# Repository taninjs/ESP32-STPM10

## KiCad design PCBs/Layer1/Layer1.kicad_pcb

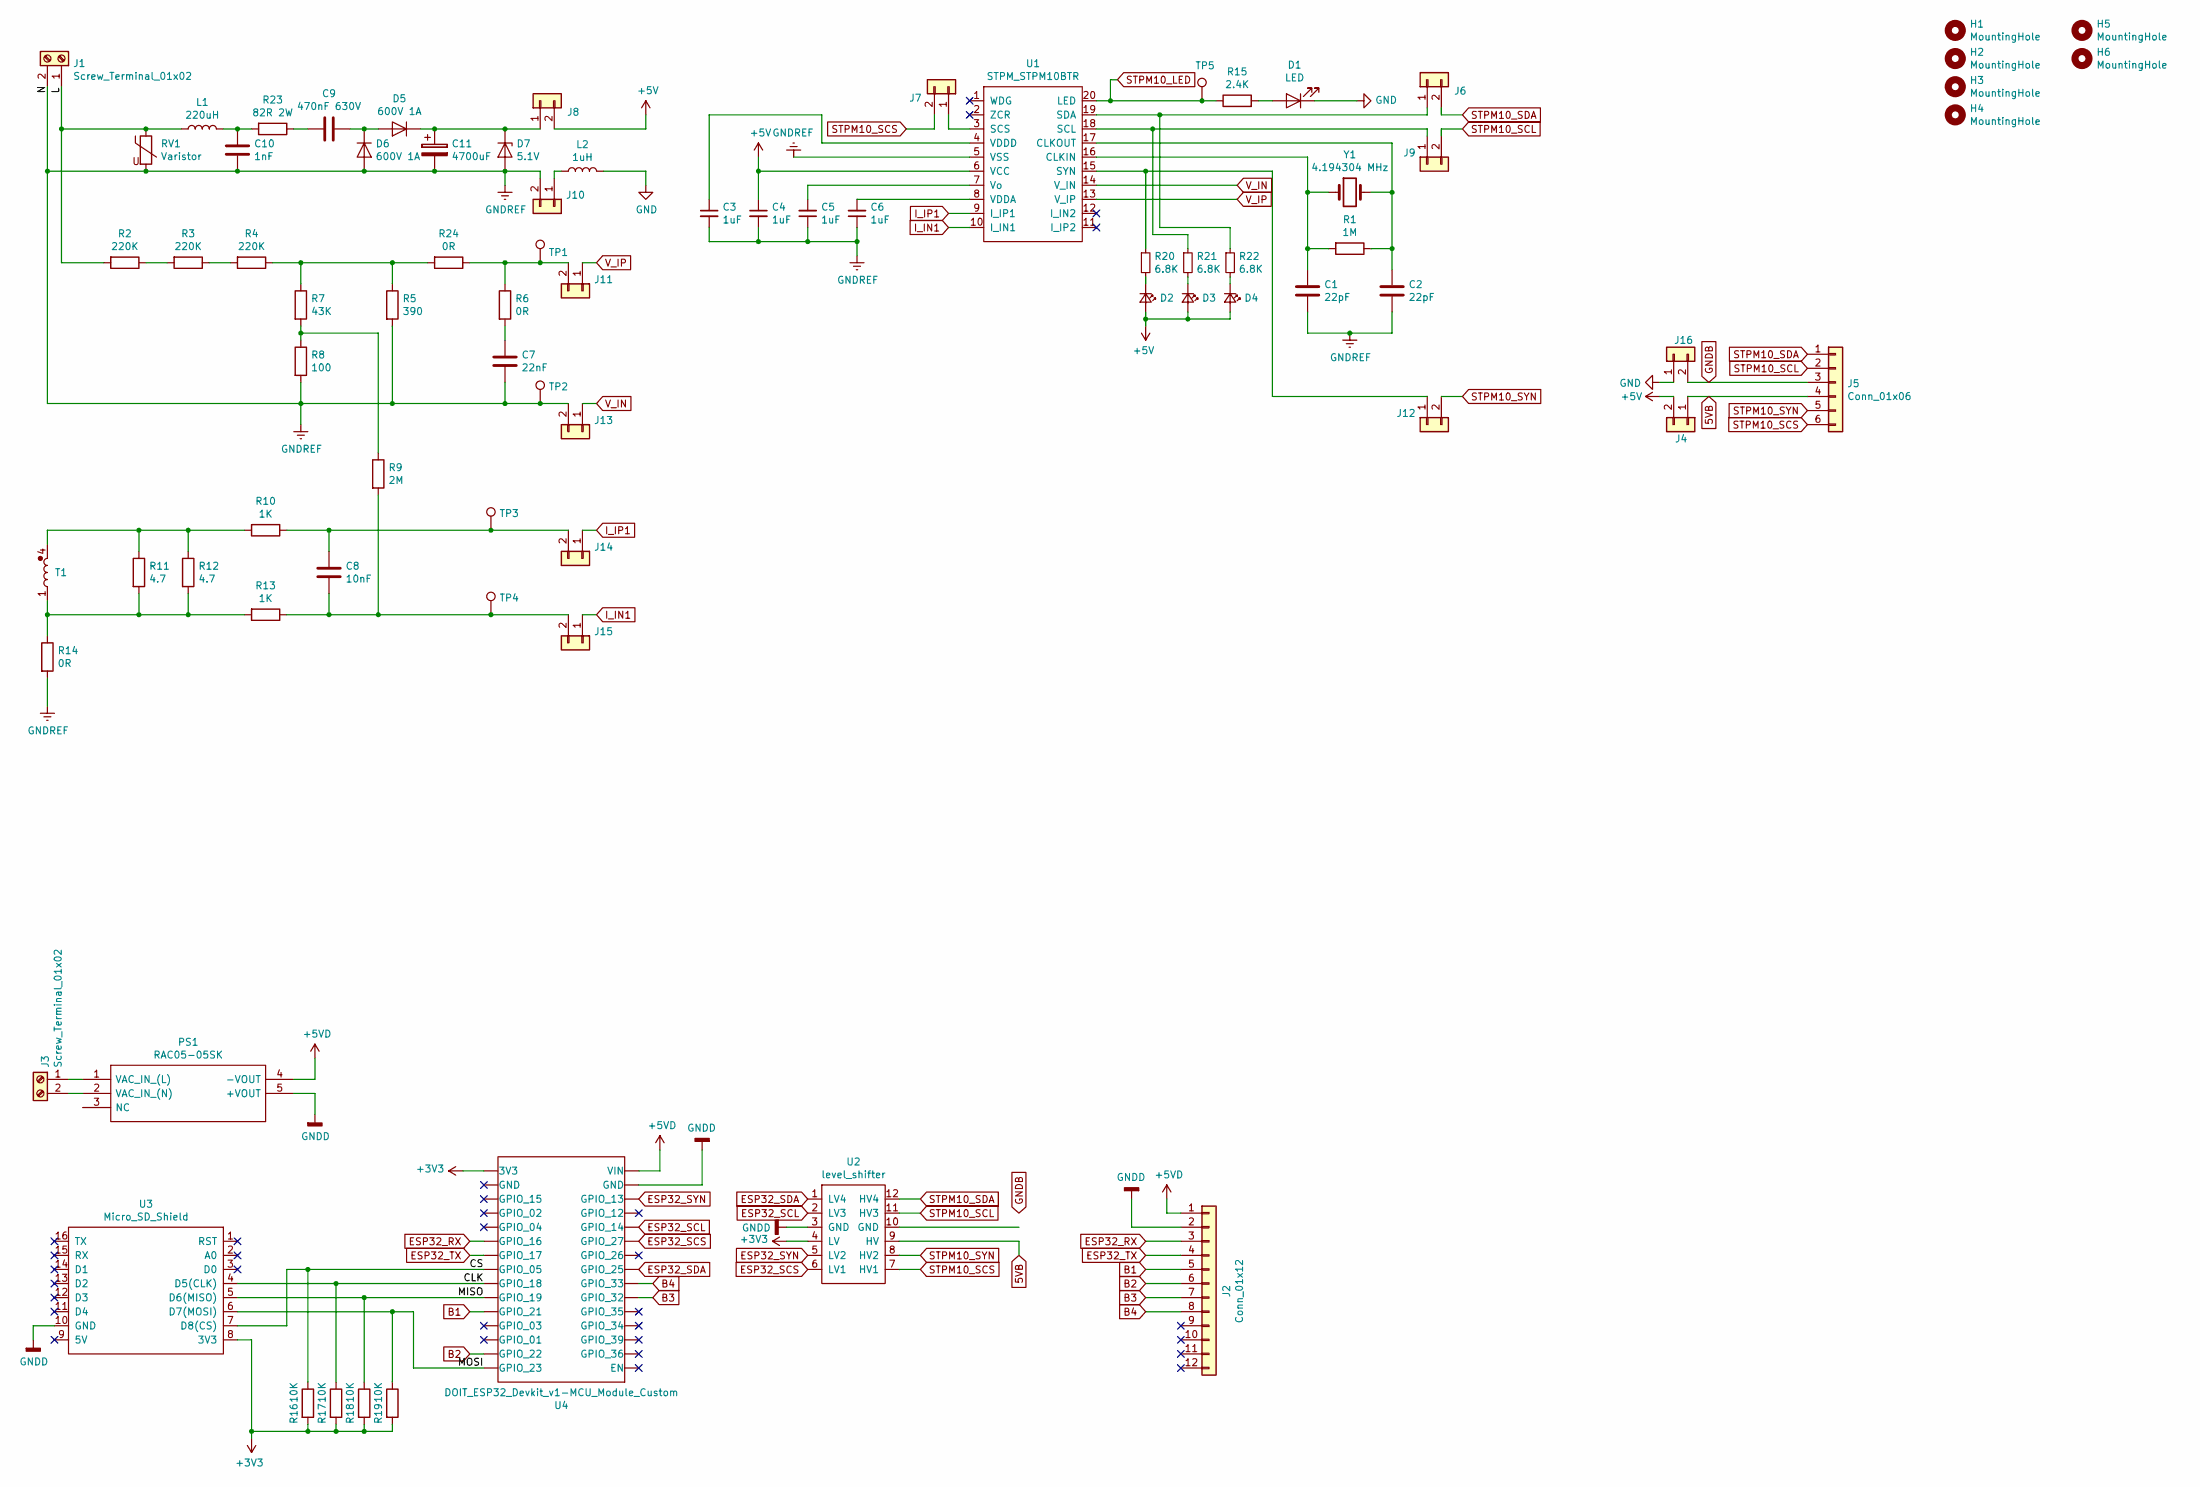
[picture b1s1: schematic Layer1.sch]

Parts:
C1, C2: 22pF; C_1206_3216Metric_Pad1.42x1.75mm_HandSolder
C3, C4, C5, C6: 1uF; C_0603_1608Metric_Pad1.05x0.95mm_HandSolder
C7: 22nF; C_1206_3216Metric_Pad1.42x1.75mm_HandSolder
C8: 10nF; C_1206_3216Metric_Pad1.42x1.75mm_HandSolder
C9: 470nF 630V; C_Rect_L26.5mm_W15.5mm_P22.50mm_MKS4
C10: 1nF; C_1806_4516Metric_Pad1.57x1.80mm_HandSolder
C11: 4700uF; CP_Radial_D12.5mm_P5.00mm
D1: LED; LED_0603_1608Metric_Pad1.05x0.95mm_HandSolder
D2, D3, D4: LED_Small; LED_0603_1608Metric_Pad1.05x0.95mm_HandSolder
D5, D6: 600V 1A; D_SMA_Handsoldering
D7: 5.1V; SOD-80
H1, H2, H3, H4, H5, H6: MountingHole; MountingHole_2.7mm_M2.5_DIN965
J1, J3: Screw_Terminal_01x02; TerminalBlock_bornier-2_P5.08mm
J2: Conn_01x12; JST_PH_B12B-PH-K_1x12_P2.00mm_Vertical
J4, J6, J7, J8, J9, J10, J11, J12, J13, J14, J15, J16: Conn_01x02; PinHeader_1x02_P2.54mm_Vertical
J5: Conn_01x06; PinHeader_1x06_P2.54mm_Vertical
L1: 220uH; L_1812_4532Metric_Pad1.30x3.40mm_HandSolder
L2: 1uH; L_1812_4532Metric_Pad1.30x3.40mm_HandSolder
PS1: RAC05-05SK; RAC05-12SK; Manufacturer_Part_Number RAC05-05SK; Mouser Part Number 919-RAC05-05SK
R1: 1M; R_1206_3216Metric_Pad1.42x1.75mm_HandSolder
R2, R3, R4: 220K; R_1206_3216Metric_Pad1.42x1.75mm_HandSolder
R5: 390; R_1206_3216Metric_Pad1.42x1.75mm_HandSolder
R6, R14, R24: 0R; R_1206_3216Metric_Pad1.42x1.75mm_HandSolder
R7: 43K; R_1206_3216Metric_Pad1.42x1.75mm_HandSolder
R8: 100; R_1206_3216Metric_Pad1.42x1.75mm_HandSolder
R9: 2M; R_Axial_DIN0204_L3.6mm_D1.6mm_P5.08mm_Horizontal
R10, R13: 1K; R_1206_3216Metric_Pad1.42x1.75mm_HandSolder
R11, R12: 4.7; R_1206_3216Metric_Pad1.42x1.75mm_HandSolder
R15: 2.4K; R_0603_1608Metric_Pad1.05x0.95mm_HandSolder
R16, R17, R18, R19: 10K; R_Axial_DIN0204_L3.6mm_D1.6mm_P5.08mm_Horizontal
R20, R21, R22: 6.8K; R_0603_1608Metric_Pad1.05x0.95mm_HandSolder
R23: 82R 2W; R_Axial_DIN0617_L17.0mm_D6.0mm_P20.32mm_Horizontal
RV1: Varistor; RV_Disc_D15.5mm_W5.9mm_P7.5mm
T1: T60404-E4624-X501
TP1, TP2, TP3, TP4, TP5: TestPoint; TestPoint_THTPad_2.0x2.0mm_Drill1.0mm
U1: STPM_STPM10BTR; TSSOP-20_4.4x6.5mm_P0.65mm
U2: level_shifter; levelshiter
U3: Micro_SD_Shield; sdcard
U4: DOIT_ESP32_Devkit_v1-MCU_Module_Custom; ESP32_DOIT_v1
Y1: 4.194304 MHz; Crystal_HC18-U_Vertical

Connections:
5VB: J4.1, J5.4, U2.9 (HV)
+3V3: R16.2, R17.2, R18.2, R19.2, U2.4 (LV), U3.8 (3V3), U4.16 (3V3)
+5V: C4.1, D2.2 (A), D3.2 (A), D4.2 (A), J4.2, J8.2, U1.6 (VCC)
+5VD: J2.1, PS1.4 (-VOUT), U4.15 (VIN)
/CLK: R17.1, U3.4 (D5(CLK)), U4.24 (GPIO_18)
/CS: R16.1, U3.7 (D8(CS)), U4.23 (GPIO_05)
/L: J1.1, L1.1, R2.2, RV1.1
/MISO: R18.1, U3.5 (D6(MISO)), U4.25 (GPIO_19)
/MOSI: R19.1, U3.6 (D7(MOSI)), U4.30 (GPIO_23)
B1: J2.5, U4.26 (GPIO_21)
B2: J2.6, U4.29 (GPIO_22)
B3: J2.7, U4.6 (GPIO_32)
B4: J2.8, U4.7 (GPIO_33)
ESP32_RX: J2.3, U4.21 (GPIO_16)
ESP32_SCL: U2.2 (LV3), U4.11 (GPIO_14)
ESP32_SCS: U2.6 (LV1), U4.10 (GPIO_27)
ESP32_SDA: U2.1 (LV4), U4.8 (GPIO_25)
ESP32_SYN: U2.5 (LV2), U4.13 (GPIO_13)
ESP32_TX: J2.4, U4.22 (GPIO_17)
GND: D1.1 (K), J16.1, L2.2
GNDB: J5.3, J16.2
GNDD: J2.2, PS1.5 (+VOUT), U2.3 (GND), U3.10 (GND), U4.14 (GND)
GNDREF: C1.2, C2.2, C3.2, C4.2, C5.1, C6.1, C7.2, C10.2, C11.2, D6.2 (A), D7.2 (A), J1.2, J10.2, J13.2, R5.2, R8.2, R14.2, RV1.2, TP2.1, U1.5 (VSS)
I_IN1: J15.1, U1.10 (I_IN1)
I_IP1: J14.1, U1.9 (I_IP1)
unnamed: C1.1, R1.2, U1.16 (CLKIN), Y1.1
unnamed: C2.1, R1.1, U1.17 (CLKOUT), Y1.2
unnamed: C3.1, U1.4 (VDDD)
unnamed: C5.2, U1.7 (Vo)
unnamed: C6.2, U1.8 (VDDA)
unnamed: C7.1, R6.2
unnamed: C8.1, J14.2, R10.1, TP3.1
unnamed: C8.2, J15.2, R9.2, R13.1, TP4.1
unnamed: C9.1, D5.2 (A), D6.1 (K)
unnamed: C9.2, R23.1
unnamed: C10.1, L1.2, R23.2
unnamed: C11.1, D5.1 (K), D7.1 (K), J8.1
unnamed: D1.2 (A), R15.2
unnamed: D2.1 (K), R20.2
unnamed: D3.1 (K), R21.2
unnamed: D4.1 (K), R22.2
unnamed: J3.1, PS1.1 (VAC_IN_(L))
unnamed: J3.2, PS1.2 (VAC_IN_(N))
unnamed: J6.1, R22.1, U1.19 (SDA)
unnamed: J7.1, U1.3 (SCS)
unnamed: J9.1, R21.1, U1.18 (SCL)
unnamed: J10.1, L2.1
unnamed: J11.2, R6.1, R24.1, TP1.1
unnamed: J12.1, R20.1, U1.15 (SYN)
unnamed: R2.1, R3.2
unnamed: R3.1, R4.2
unnamed: R7.2, R8.1, R9.1
unnamed: R10.2, R11.1, R12.1, T1.4
unnamed: R11.2, R12.2, R13.2, R14.1, T1.1
unnamed: R4.1, R5.1, R7.1, R24.2
STPM10_LED: R15.1, TP5.1, U1.20 (LED)
STPM10_SCL: J5.2, J9.2, U2.11 (HV3)
STPM10_SCS: J5.6, J7.2, U2.7 (HV1)
STPM10_SDA: J5.1, J6.2, U2.12 (HV4)
STPM10_SYN: J5.5, J12.2, U2.8 (HV2)
V_IN: J13.1, U1.14 (V_IN)
V_IP: J11.1, U1.13 (V_IP)

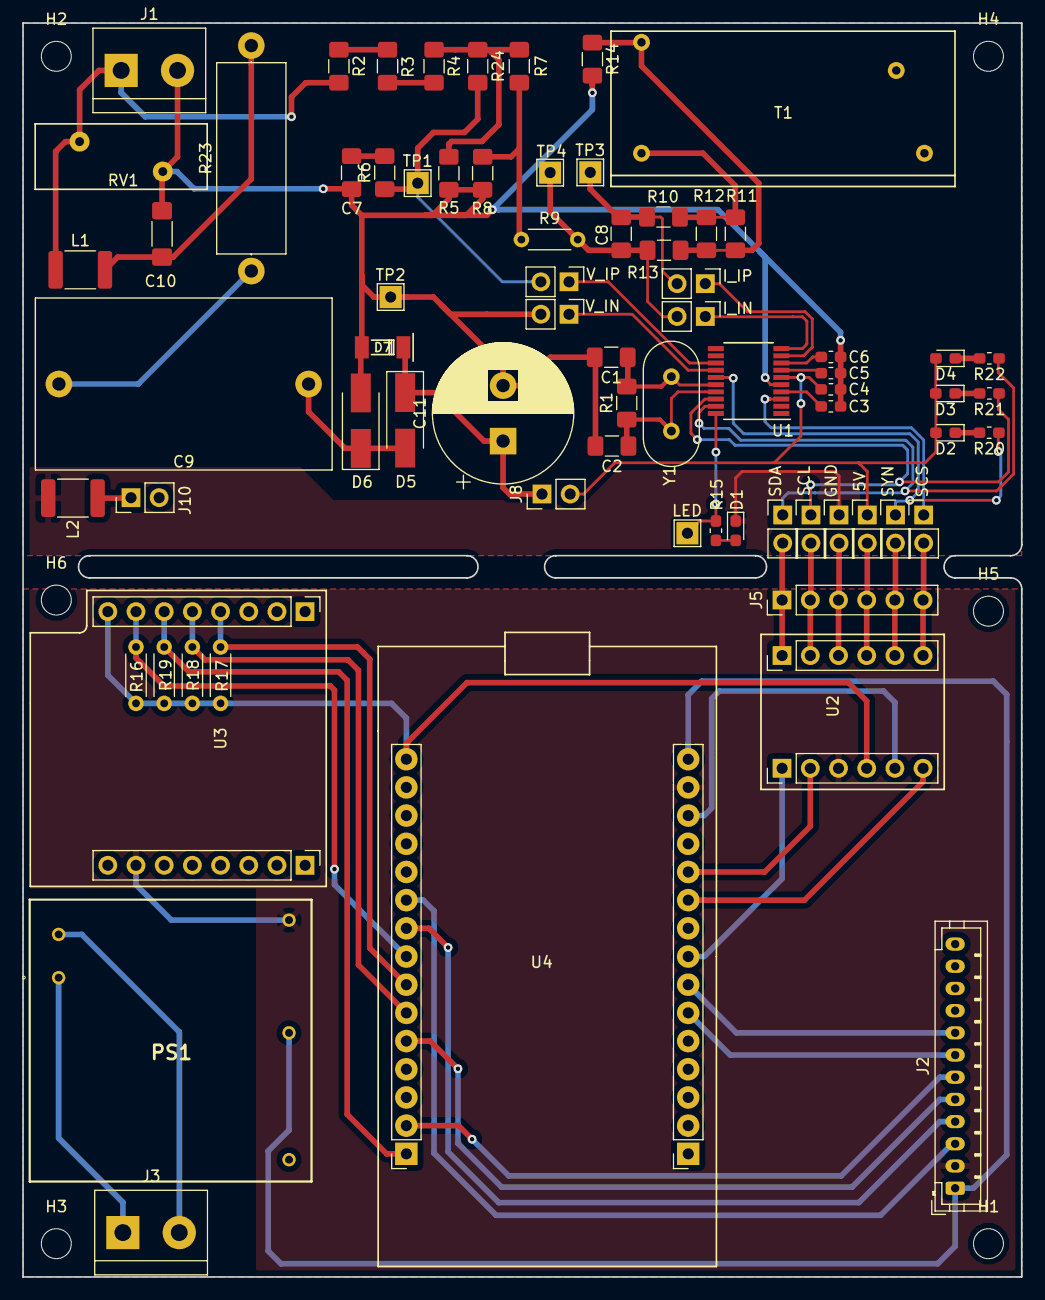
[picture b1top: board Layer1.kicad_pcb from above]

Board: 2 copper layers, 90.0 x 113.0 mm, 79 parts (0 on the bottom side), 62 nets.

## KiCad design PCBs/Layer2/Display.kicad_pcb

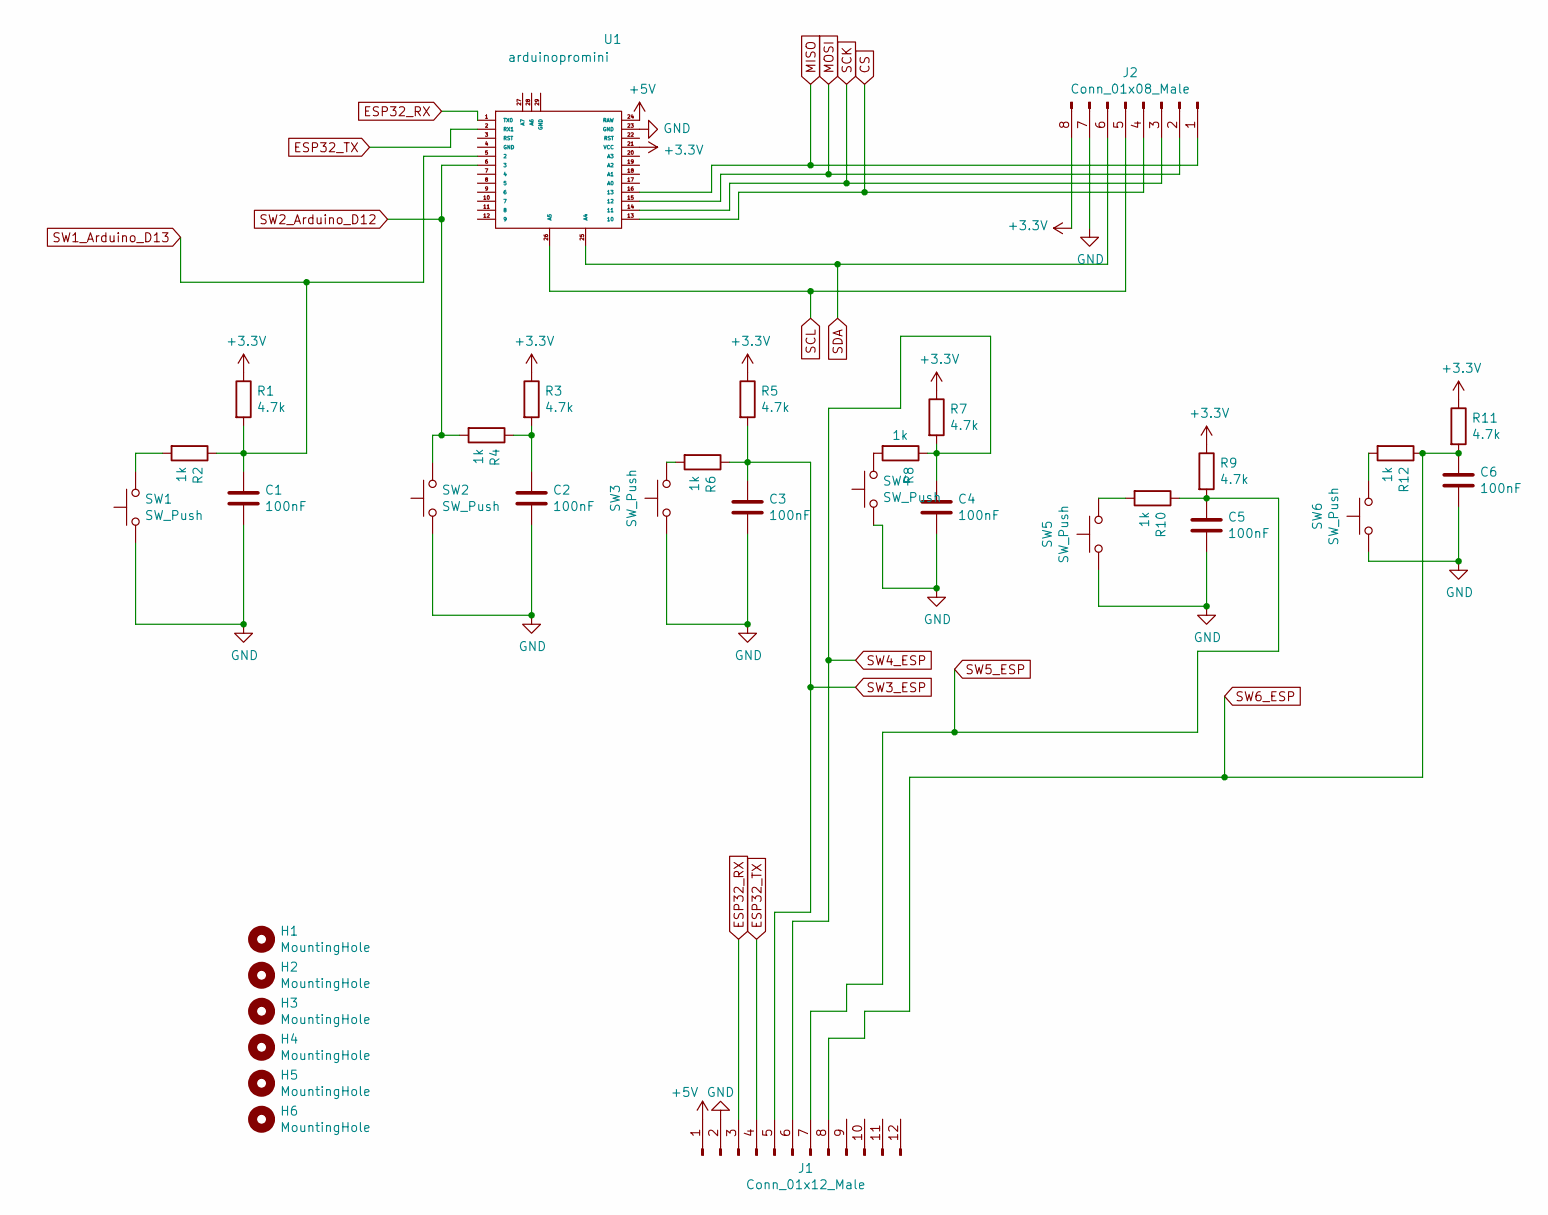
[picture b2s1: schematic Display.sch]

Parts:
C1, C2, C3, C4, C5, C6: 100nF; C_1206_3216Metric_Pad1.42x1.75mm_HandSolder
H1, H2, H3, H4, H5, H6: MountingHole; MountingHole_2.7mm_M2.5_DIN965
J1: Conn_01x12_Male; PinHeader_1x12_P2.54mm_Vertical
J2: Conn_01x08_Male; PinHeader_1x08_P2.54mm_Vertical
R1, R3, R5, R7, R9, R11: 4.7k; R_1206_3216Metric_Pad1.42x1.75mm_HandSolder
R2, R4, R6, R8, R10, R12: 1k; R_1206_3216Metric_Pad1.42x1.75mm_HandSolder
SW1, SW2, SW3, SW4, SW5, SW6: SW_Push; SW_PUSH-12mm_Wuerth-430476085716
U1: arduinopromini

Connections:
+3V3: J2.8, R1.1, R3.1, R5.1, R7.1, R9.1, R11.1, U1.21 (VCC)
+5V: J1.1, U1.24 (RAW)
CS: J2.4, U1.13 (10)
ESP32_RX: J1.3, U1.1 (TX0)
ESP32_TX: J1.4, U1.2 (RX1)
GND: C1.2, C2.2, C3.2, C4.2, C5.2, C6.2, J1.2, J2.7, SW1.1, SW2.1, SW3.1, SW4.1, SW5.1, SW6.1, U1.23 (GND)
MISO: J2.1, U1.16 (13)
MOSI: J2.2, U1.15 (12)
unnamed: C2.1, R3.2, R4.1
unnamed: R2.2, SW1.2
unnamed: R6.2, SW3.2
unnamed: R8.2, SW4.2
unnamed: R10.2, SW5.2
unnamed: R12.2, SW6.2
SCK: J2.3, U1.14 (11)
SCL: J2.5, U1.26 (A5)
SDA: J2.6, U1.25 (A4)
SW1_Arduino_D13: C1.1, R1.2, R2.1, U1.5 (2)
SW2_Arduino_D12: R4.2, SW2.2, U1.6 (3)
SW3_ESP: C3.1, J1.5, R5.2, R6.1
SW4_ESP: C4.1, J1.6, R7.2, R8.1
SW5_ESP: C5.1, J1.7, R9.2, R10.1
SW6_ESP: C6.1, J1.8, R11.2, R12.1

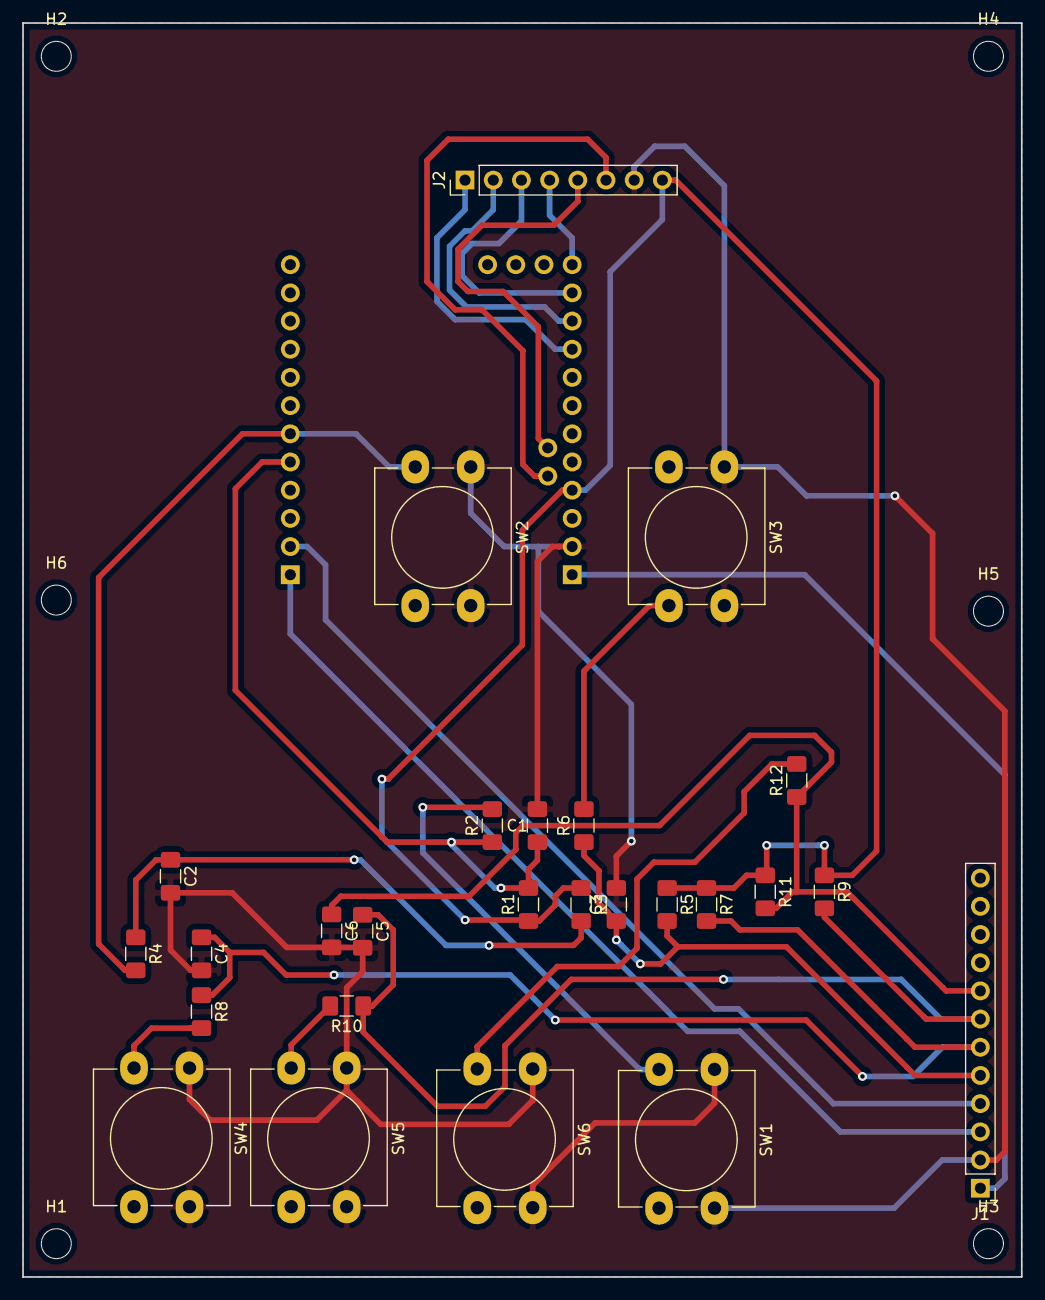
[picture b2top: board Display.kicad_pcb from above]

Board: 2 copper layers, 90.0 x 113.0 mm, 33 parts (1 on the bottom side), 23 nets.

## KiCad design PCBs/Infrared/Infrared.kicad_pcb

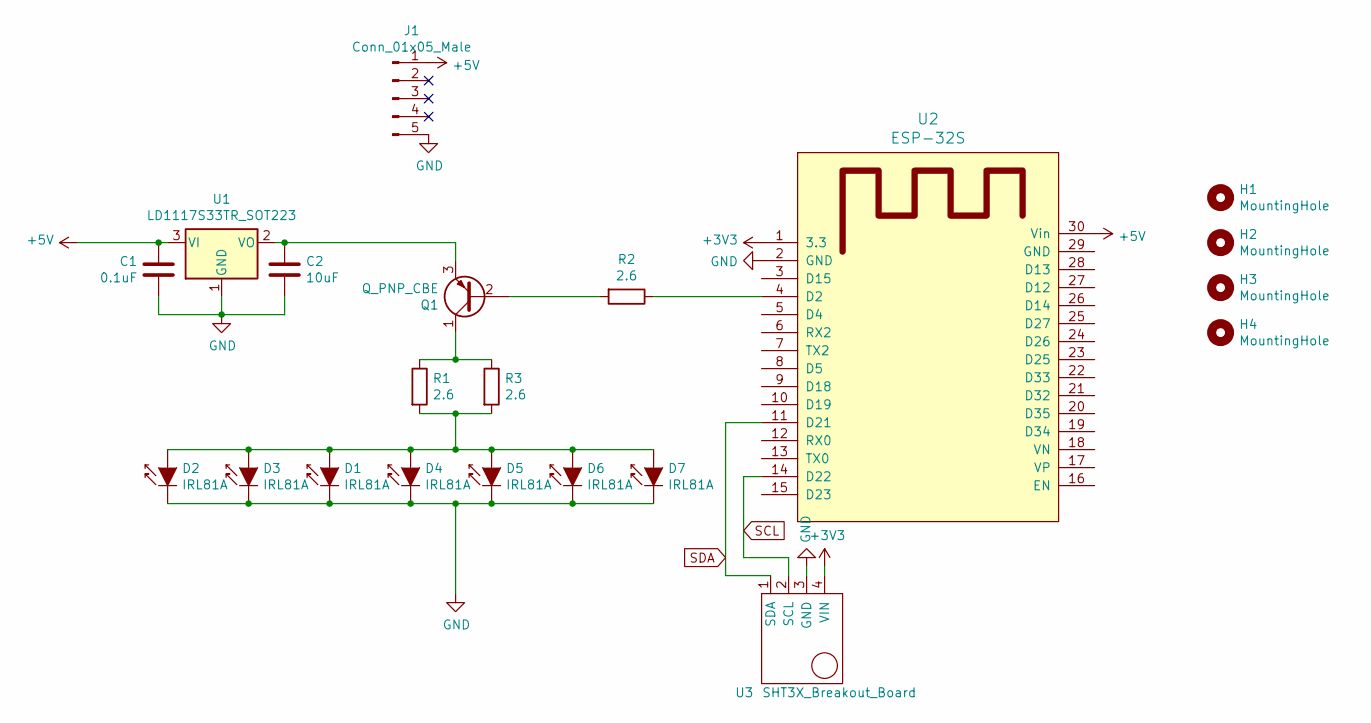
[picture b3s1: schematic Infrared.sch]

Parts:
C1: 0.1uF; CP_Radial_D5.0mm_P2.50mm
C2: 10uF; CP_Radial_D5.0mm_P2.50mm
D1, D2, D3, D4, D5, D6, D7: IRL81A; LED_D3.0mm_IRGrey
H1, H2, H3, H4: MountingHole; MountingHole_3.2mm_M3_DIN965
J1: Conn_01x05_Male; PinHeader_1x05_P2.54mm_Vertical
Q1: Q_PNP_CBE; TO-92L_Inline_Wide
R1, R2, R3: 2.6; R_Axial_DIN0204_L3.6mm_D1.6mm_P7.62mm_Horizontal
U1: LD1117S33TR_SOT223; TO-220-3_Vertical
U2: ESP-32S; ESP32_DOIT_v1
U3: SHT3X_Breakout_Board; PinHeader_1x04_P2.54mm_Vertical

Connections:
+3V3: U2.1 (3.3), U3.4 (VIN)
+5V: C1.1, J1.1, U1.3 (VI), U2.30 (Vin)
GND: C1.2, C2.2, D1.1 (K), D2.1 (K), D3.1 (K), D4.1 (K), D5.1 (K), D6.1 (K), D7.1 (K), J1.5, U1.1 (GND), U2.2 (GND), U3.3 (GND)
unnamed: C2.1, Q1.3 (E), U1.2 (VO)
unnamed: D1.2 (A), D2.2 (A), D3.2 (A), D4.2 (A), D5.2 (A), D6.2 (A), D7.2 (A), R1.2, R3.2
unnamed: Q1.1 (C), R1.1, R3.1
unnamed: Q1.2 (B), R2.2
unnamed: R2.1, U2.4 (D2)
SCL: U2.14 (D22), U3.2 (SCL)
SDA: U2.11 (D21), U3.1 (SDA)

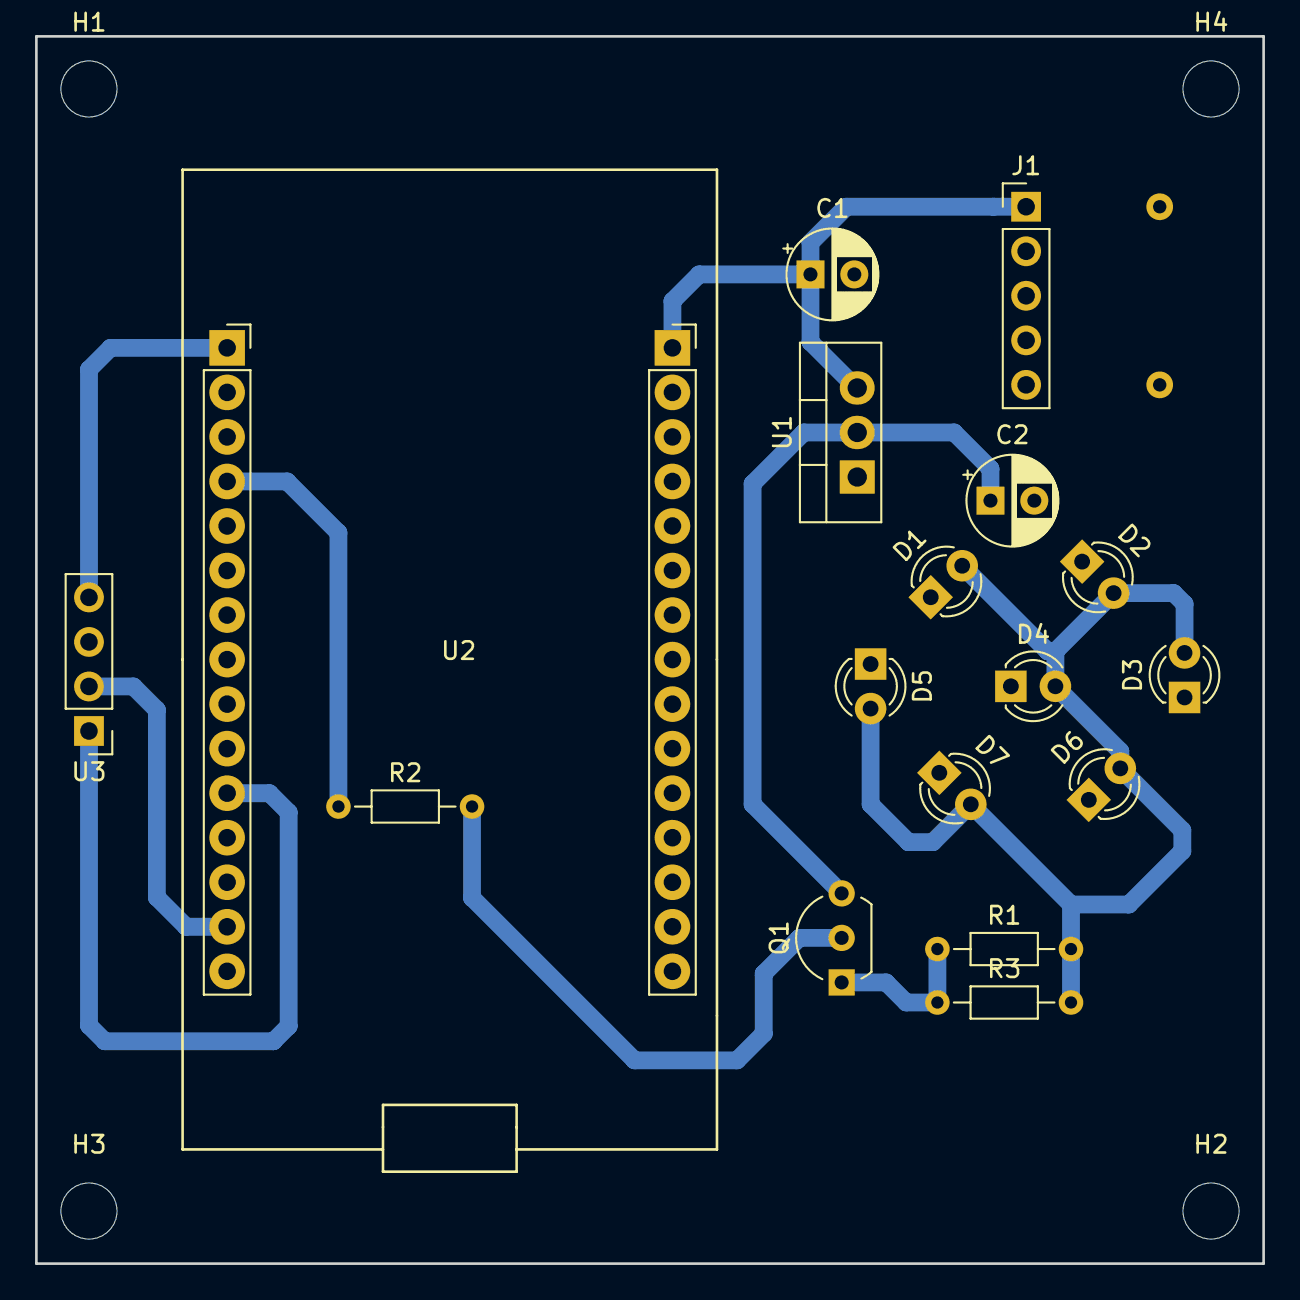
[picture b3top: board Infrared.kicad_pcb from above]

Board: 2 copper layers, 70.0 x 70.0 mm, 21 parts (0 on the bottom side), 10 nets.

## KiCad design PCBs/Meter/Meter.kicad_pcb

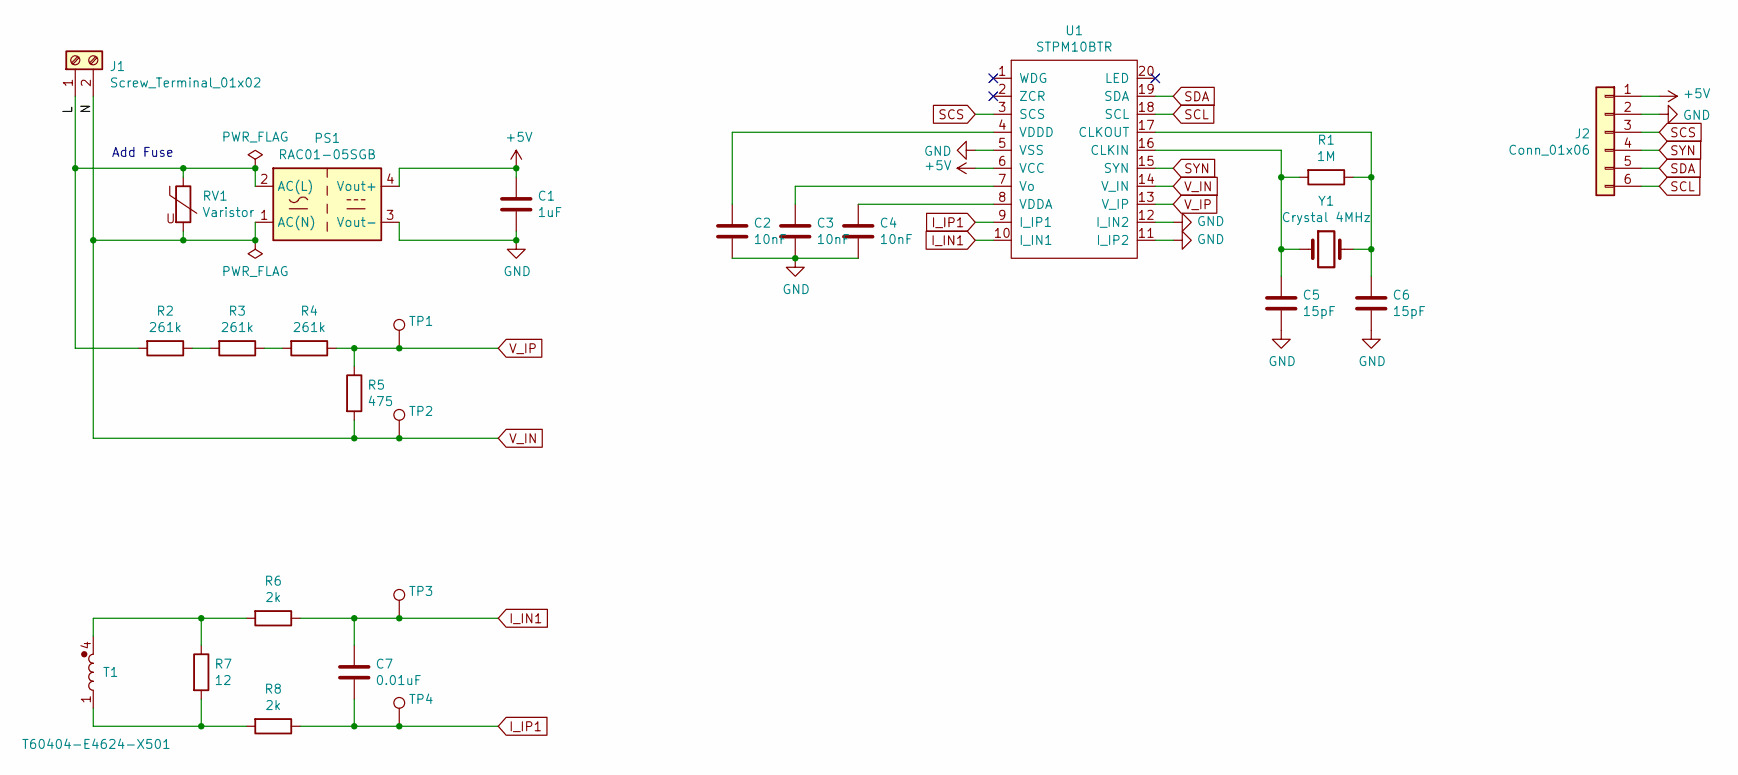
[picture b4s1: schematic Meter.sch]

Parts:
C1: 1uF; C_1206_3216Metric_Pad1.42x1.75mm_HandSolder
C2, C3, C4: 10nF; C_0603_1608Metric_Pad1.05x0.95mm_HandSolder
C5, C6: 15pF; C_0603_1608Metric_Pad1.05x0.95mm_HandSolder
C7: 0.01uF; C_0603_1608Metric_Pad1.05x0.95mm_HandSolder
J1: Screw_Terminal_01x02; TerminalBlock_Phoenix_MKDS-1,5-2-5.08_1x02_P5.08mm_Horizont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
J2: Conn_01x06; PinHeader_1x06_P2.54mm_Vertical
PS1: RAC01-05SGB; Converter_ACDC_RECOM_RAC01-xxSGB_THT
R1: 1M; R_0603_1608Metric_Pad1.05x0.95mm_HandSolder
R2, R3, R4: 261k; R_1206_3216Metric_Pad1.42x1.75mm_HandSolder
R5: 475; R_0603_1608Metric_Pad1.05x0.95mm_HandSolder
R6, R8: 2k; R_1206_3216Metric_Pad1.42x1.75mm_HandSolder
R7: 12; R_0603_1608Metric_Pad1.05x0.95mm_HandSolder
RV1: Varistor; RV_Disc_D15.5mm_W5.9mm_P7.5mm
T1: T60404-E4624-X501
TP1, TP2, TP3, TP4: TestPoint; TestPoint_THTPad_D2.0mm_Drill1.0mm
U1: STPM10BTR; TSSOP-20_4.4x6.5mm_P0.65mm
Y1: Crystal 4MHz; Crystal_HC18-U_Vertical

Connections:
+5V: C1.1, J2.1, PS1.4 (Vout+), U1.6 (VCC)
/L: J1.1, PS1.2 (AC(L)), R2.2, RV1.1
GND: C1.2, C2.2, C3.2, C4.2, C5.2, C6.2, J2.2, PS1.3 (Vout-), U1.5 (VSS), U1.11 (I_IP2), U1.12 (I_IN2)
I_IN1: C7.1, R6.1, TP3.1, U1.10 (I_IN1)
I_IP1: C7.2, R8.1, TP4.1, U1.9 (I_IP1)
unnamed: C2.1, U1.4 (VDDD)
unnamed: C3.1, U1.7 (Vo)
unnamed: C4.1, U1.8 (VDDA)
unnamed: C5.1, R1.2, U1.16 (CLKIN), Y1.1
unnamed: C6.1, R1.1, U1.17 (CLKOUT), Y1.2
unnamed: R2.1, R3.2
unnamed: R3.1, R4.2
unnamed: R6.2, R7.1, T1.4
unnamed: R7.2, R8.2, T1.1
SCL: J2.6, U1.18 (SCL)
SCS: J2.3, U1.3 (SCS)
SDA: J2.5, U1.19 (SDA)
SYN: J2.4, U1.15 (SYN)
V_IN: J1.2, PS1.1 (AC(N)), R5.2, RV1.2, TP2.1, U1.14 (V_IN)
V_IP: R4.1, R5.1, TP1.1, U1.13 (V_IP)

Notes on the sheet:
Add Fuse

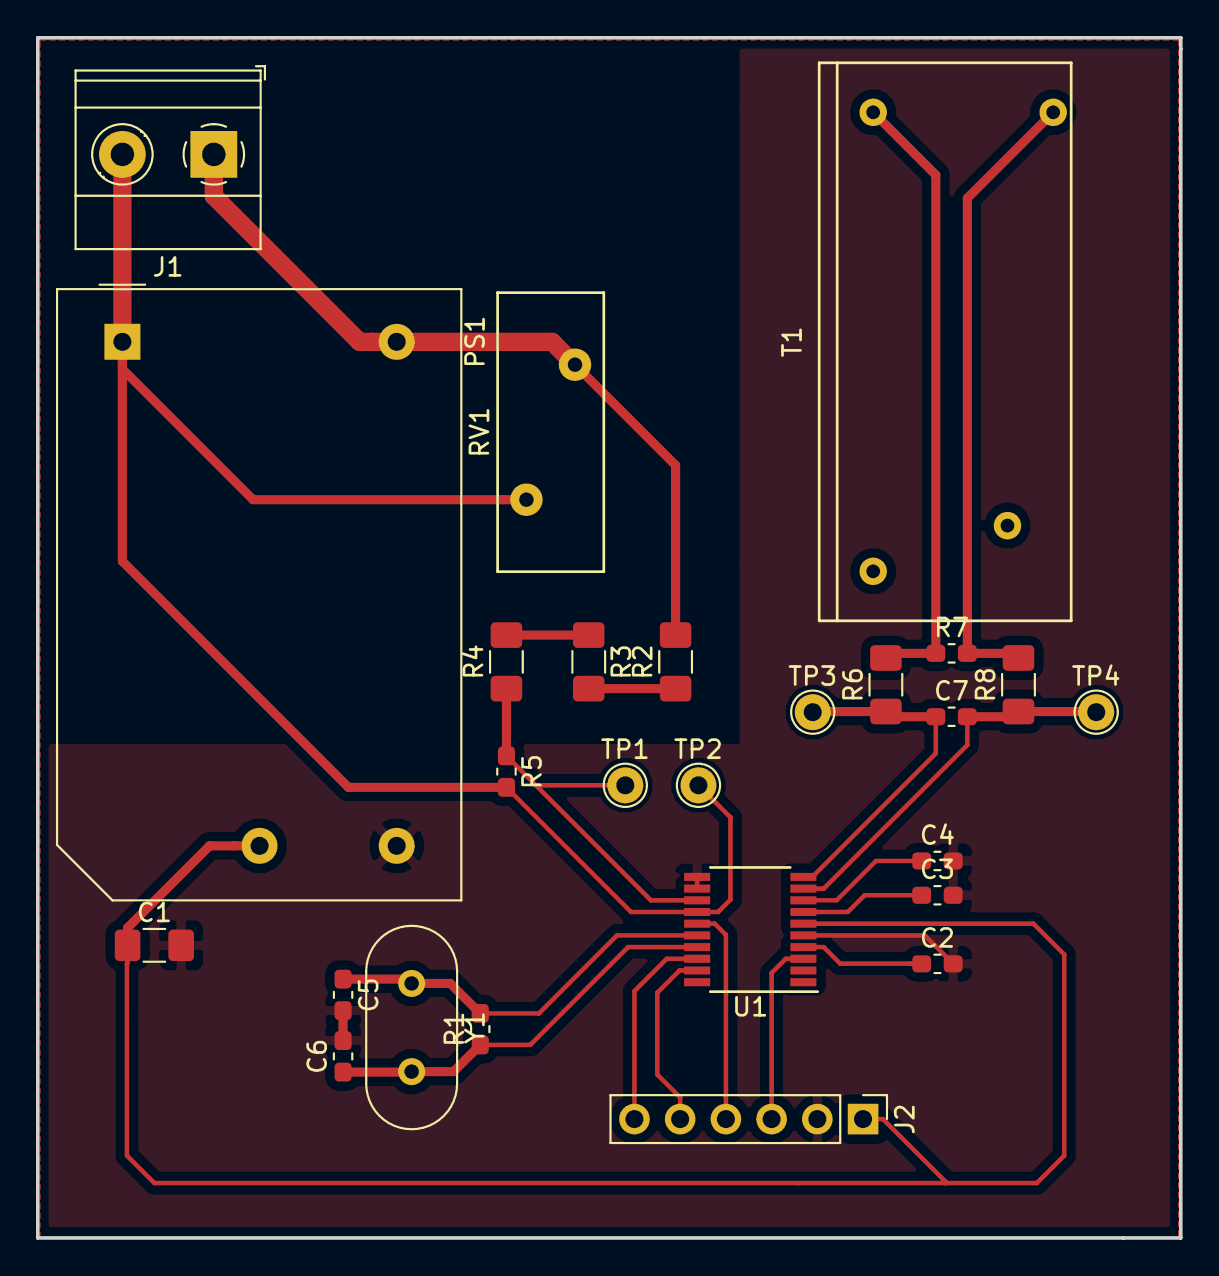
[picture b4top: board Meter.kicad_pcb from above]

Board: 2 copper layers, 63.5 x 66.7 mm, 26 parts (0 on the bottom side), 20 nets.

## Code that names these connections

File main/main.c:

#include <stdio.h>
#include <string.h>

#include "freertos/FreeRTOS.h"
#include "freertos/task.h"
#include "driver/gpio.h"
#include "driver/spi_master.h"
#include "sdkconfig.h"
#include "esp32/rom/ets_sys.h"
#include "stpm10.h"
#include "http.h"
#include "wifi.h"
#include "nvs_flash.h"
#include "driver/timer.h"
#include "sd.h"
#include "driver/uart.h"

#define STPM10_SYN GPIO_NUM_13
#define STPM10_SCK GPIO_NUM_14
#define STPM10_SDA GPIO_NUM_25
#define STPM10_SCS GPIO_NUM_27

#define SDHC_D8_CS   5
#define SDHC_D5_SCK  18
#define SDHC_D6_MISO 19
#define SDHC_D7_MOSI 23

#define UART_TX GPIO_NUM_17
#define UART_RX GPIO_NUM_16

#define STPM10_ENERGY_CALIBRATOR 5.7837e-6 // K_AW active energy [unit] Whr/digit
// #define STPM10_ENERGY_CALIBRATOR 5.82566e-6 

spi_device_handle_t spi;
uint32_t stpm10_data[8];
uint64_t stpm10_type0_energy_counter = 0;

typedef struct {
	long new;
	long old;   // previous energy value
	double total;	// Wh
} ENERGY;

ENERGY active_energy   = { .new = 0, .old = 0, .total = 0 };
ENERGY reactive_energy = { .new = 0, .old = 0, .total = 0 };
ENERGY apparent_energy = { .new = 0, .old = 0, .total = 0 };
double P, Q, S;		// Active Power (P), Reactive Power (Q), Apparent Power (S)
double pf;			// power factors
int apptime = 0;
unsigned long long energy_counter = 0;

void meter_task(void *pvParameter) {
	stpm10_spi_config_t stpm10_cfg = {
		.SCS = STPM10_SCS,
		.SYN = STPM10_SYN,
		.SCK = STPM10_SCK,
		.SDA = STPM10_SDA,
		.spi = spi
	};

	stpm10_init(stpm10_cfg, WRITE);
	vTaskDelay(1000 / portTICK_PERIOD_MS);

	stpm10_write(47, 1);
	stpm10_write(47, 1);

	/* Write STPM10 current calibration bits */
	for (int i = 0; i < 8; i++) {
		stpm10_write(CHP + i, (0x90 >> i) & 0x01);
	}

	/* Write STPM10 voltage calibration bits */
	for (int i = 0; i < 8; i++) {
		stpm10_write(CHV + i, (0x8F >> i) & 0x01);
	}
	

	stpm10_enter_read_mode();
	vTaskDelay(1000 / portTICK_PERIOD_MS);

	// start timer
	timer_config_t timer00_cfg = {
		.divider = 80,
		.counter_dir = TIMER_COUNT_UP,
		.counter_en = TIMER_PAUSE,
		.auto_reload = 0,
	};
	timer_init(TIMER_GROUP_0, TIMER_0, &timer00_cfg);
	timer_set_counter_value(TIMER_GROUP_0, TIMER_0, 0x00000000ULL);
	timer_start(TIMER_GROUP_0, TIMER_0);

	for (;;) {
		double dt = 0;
		// Re-read until pass parity check
		do {
			stpm10_read(stpm10_data, 8);

			// get timer interval and scale unit to hr
			// dt [unit]s * 1 [unit]hr / 3600.0 [unit]s => dt [unit]hr
			timer_get_counter_time_sec(TIMER_GROUP_0, TIMER_0, &dt);
			dt = dt / 3600.0;
		} while (!(
			stpm10_parity_check(stpm10_data[0]) && stpm10_parity_check(stpm10_data[1]) &&
			stpm10_parity_check(stpm10_data[2]) && stpm10_parity_check(stpm10_data[3]) &&
			stpm10_parity_check(stpm10_data[4]) && stpm10_parity_check(stpm10_data[5]) &&
			stpm10_parity_check(stpm10_data[6]) && stpm10_parity_check(stpm10_data[7])
		));

		// reset timer
		timer_set_counter_value(TIMER_GROUP_0, TIMER_0, 0x00000000ULL);

		int x_i_rms = (stpm10_data[DEV] & 0xFFFF);
		if (!__STPM10_IS_NO_LOAD(stpm10_data) && x_i_rms > 10) {

			active_energy.new = __STPM10_GET_ACTIVE_ENERGY(stpm10_data);
			reactive_energy.new = __STPM10_GET_REACTIVE_ENERGY(stpm10_data);
			apparent_energy.new = __STPM10_GET_APPARENT_ENERGY(stpm10_data);

			double dEa = 0;
			if (active_energy.new > active_energy.old){
				dEa = ((active_energy.new   - active_energy.old  ) & 0x000FFFFF) * STPM10_ENERGY_CALIBRATOR; // [unit]Watt-hr
			}
			double dEr = ((reactive_energy.new - reactive_energy.old) & 0x000FFFFF) * STPM10_ENERGY_CALIBRATOR * 2; // [unit]VAR-hr
			double dEs = ((apparent_energy.new - apparent_energy.old) & 0x000FFFFF) * STPM10_ENERGY_CALIBRATOR; // [unit]VA-hr

			energy_counter += ((active_energy.new   - active_energy.old) & 0x000FFFFF);

			P = dEa/dt; // [unit]Watt
			Q = dEr/dt; // [unit]Watt
			S = dEs/dt; // [unit]Watt
			pf = P/S;

			active_energy.total +=  dEa;
			reactive_energy.total += dEr;
			apparent_energy.total += dEs;
			stpm10_type0_energy_counter += __STPM10_GET_ACTIVE_ENERGY(stpm10_data);

			active_energy.old = active_energy.new;
			reactive_energy.old = reactive_energy.new;
			apparent_energy.old = apparent_energy.new;
		} else {
			P = 0.0;
			Q = 0.0;
			S = 0.0;
		}

		vTaskDelay(20 / portTICK_PERIOD_MS);
	}
}

void print_task(void *pvParameter)
{
	for(;;) {
		for (int i = 0; i < 8; i++) printf("%#.8x\n", stpm10_data[i]);

		int x_u_rms = (stpm10_data[DEV] >> 16) & 0x7FF;
		int x_i_rms = (stpm10_data[DEV] & 0xFFFF);

		printf("config bits: %.7x%.7x\n", stpm10_data[CFH] & 0x0FFFFFFF, stpm10_data[CFL] & 0x0FFFFFFF);
		printf("uRMS: %d (digital), %f V\n", x_u_rms, stpm10_read_vrms(stpm10_data));
		printf("iRMS: %d (digital), %f A\n", x_i_rms, stpm10_read_irms(stpm10_data));
		printf("freq: %f Hz\n", stpm10_read_freq(stpm10_data));

		printf("Active Energy: %f Wh\n", active_energy.total);
		printf("Active Energy: %llu (digital)", stpm10_type0_energy_counter);
		printf("Reactive Energy: %f Wh\n", reactive_energy.total);
		printf("Apparent Energy: %f Wh\n", apparent_energy.total);

		printf("P: %.4f, Q: %.4f, S: %.4f\n", P, Q, S);
		printf("pf: %.2f\n\n", pf);

		printf("time: %d, energy_counter: %llu, active_energy: %.5f\n", apptime, energy_counter, active_energy.total / 1000.0);
		vTaskDelay(3000 / portTICK_PERIOD_MS);
	}
}

void http_task(void *pvParameter)
{
	app_wifi_wait_connected();
	ESP_LOGI("MAIN", "Connected to AP, begin HTTP example");

	for(;;) {
		float vrms = stpm10_read_vrms(stpm10_data);
		float irms = stpm10_read_irms(stpm10_data);

		http_post(active_energy.total, vrms, irms, P, Q, S, pf, __STPM10_IS_NO_LOAD(stpm10_data));
		vTaskDelay(3000 / portTICK_PERIOD_MS);
	}
}

void sd_task(void *pvParameter)
{
	sd_config_t sd_cfg = {
		.MISO = SDHC_D6_MISO,
		.MOSI = SDHC_D7_MOSI,
		.SCK = SDHC_D5_SCK,
		.CS = SDHC_D8_CS
	};

	sd_init(sd_cfg);
	sd_clear_energy_record();
	active_energy.total = sd_read_total_energy(ACTIVE);
	reactive_energy.total = sd_read_total_energy(REACTIVE);
	apparent_energy.total = sd_read_total_energy(APPARENT);

	for (;;) {
		sd_save_total_energy(apparent_energy.total, reactive_energy.total, apparent_energy.total);
		sd_save_energy_record(apptime, energy_counter, active_energy.total);
		vTaskDelay(1000 / portTICK_PERIOD_MS);
		apptime += 1;
	}
}

void uart_task(void *pvParameter)
{
	uart_config_t config = {
		.baud_rate = 9600,
		.data_bits = UART_DATA_8_BITS,
		.parity    = UART_PARITY_DISABLE,
		.stop_bits = UART_STOP_BITS_1,
		.flow_ctrl = UART_HW_FLOWCTRL_DISABLE
	};

	uart_param_config(UART_NUM_1, &config);
	uart_set_pin(UART_NUM_1, UART_TX, UART_RX, UART_PIN_NO_CHANGE, UART_PIN_NO_CHANGE);
	uart_driver_install(UART_NUM_1, 2048, 0, 0, NULL, 0);

	for (;;) {
		char msg[80];
		sprintf(msg, "%.2f;%.2f;%.2f;%.2f;%.2f;%.2f;%.2f;\n",
				stpm10_read_vrms(stpm10_data),
				stpm10_read_irms(stpm10_data),
				stpm10_read_freq(stpm10_data),
				S,
				P,
				Q,
				active_energy.total
		);
		// sprintf(msg, "%.2f;%.2f;%.2f;%.2f;%.2f;%.2f;%.2f;\n",
		// 		1.00,
		// 		2.00,
		// 		3.00,
		// 		5.00,
		// 		4.00,
		// 		6.00,
		// 		7.00
		// );
		uart_write_bytes(UART_NUM_1, msg, strlen(msg));
		vTaskDelay(1500 / portTICK_PERIOD_MS);
	}
}

void app_main() {
	/* Initialize Non-Volatile Flash */
	esp_err_t ret = nvs_flash_init();
	if (ret == ESP_ERR_NVS_NO_FREE_PAGES || ret == ESP_ERR_NVS_NEW_VERSION_FOUND) {
	  ESP_ERROR_CHECK(nvs_flash_erase());
	  ret = nvs_flash_init();
	}
	ESP_ERROR_CHECK(ret);

	/* Initialize WIFI connection */
	app_wifi_initialise();

	/* Initialize Tasks */
	xTaskCreate(&sd_task, "sd_task", 4096, NULL, 4, NULL);
	xTaskCreate(&meter_task, "meter_task", 4096, NULL, 5, NULL);
	xTaskCreate(&print_task, "print_task", 2048, NULL, 3, NULL);
	xTaskCreate(&http_task, "http_task", 8192, NULL, 4, NULL);
	xTaskCreate(&uart_task, "uart_task", 2048, NULL, 3, NULL);
}

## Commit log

2019-02-11 Add PCBs
2019-03-09 Add sd card
2019-03-10 add lib folder
2019-03-10 Add ESP32 footprint
2019-03-10 add meter symbols
2019-03-10 add layer 1 project
2019-03-10 rename rescue
2019-03-10 add arduino level shifter sd card footprint
2019-03-10 add arduino levelshifter sd card symbol
2019-03-10 add power supply RAC05-05SK lib, footprint
2019-03-10 update esp32, sd-card-shield, levelshifter footprint
2019-03-10 Layer1 Ver1.0
2019-03-10 add layer 2
2019-03-16 WIP: version 2
2019-03-16 WIP: version 2 schematics
2019-03-18 Layer 1 Ver2, waiting for review
2019-03-18 add infrared project
2019-03-18 Auto stash before merge of "master" and "origin/master"
2019-03-18 Infared PCB
2019-03-18 display update
2019-03-18 layer 2 update
2019-03-19 WIP add pinheader
2019-03-19 Layer1 -- Ready to order
2019-04-03 update PCB Layer1
2019-04-03 minor change for esp32 code
2019-04-04 WIP: for calibration
2019-04-04 FIX Conflict
2019-04-19 VER 1.0
